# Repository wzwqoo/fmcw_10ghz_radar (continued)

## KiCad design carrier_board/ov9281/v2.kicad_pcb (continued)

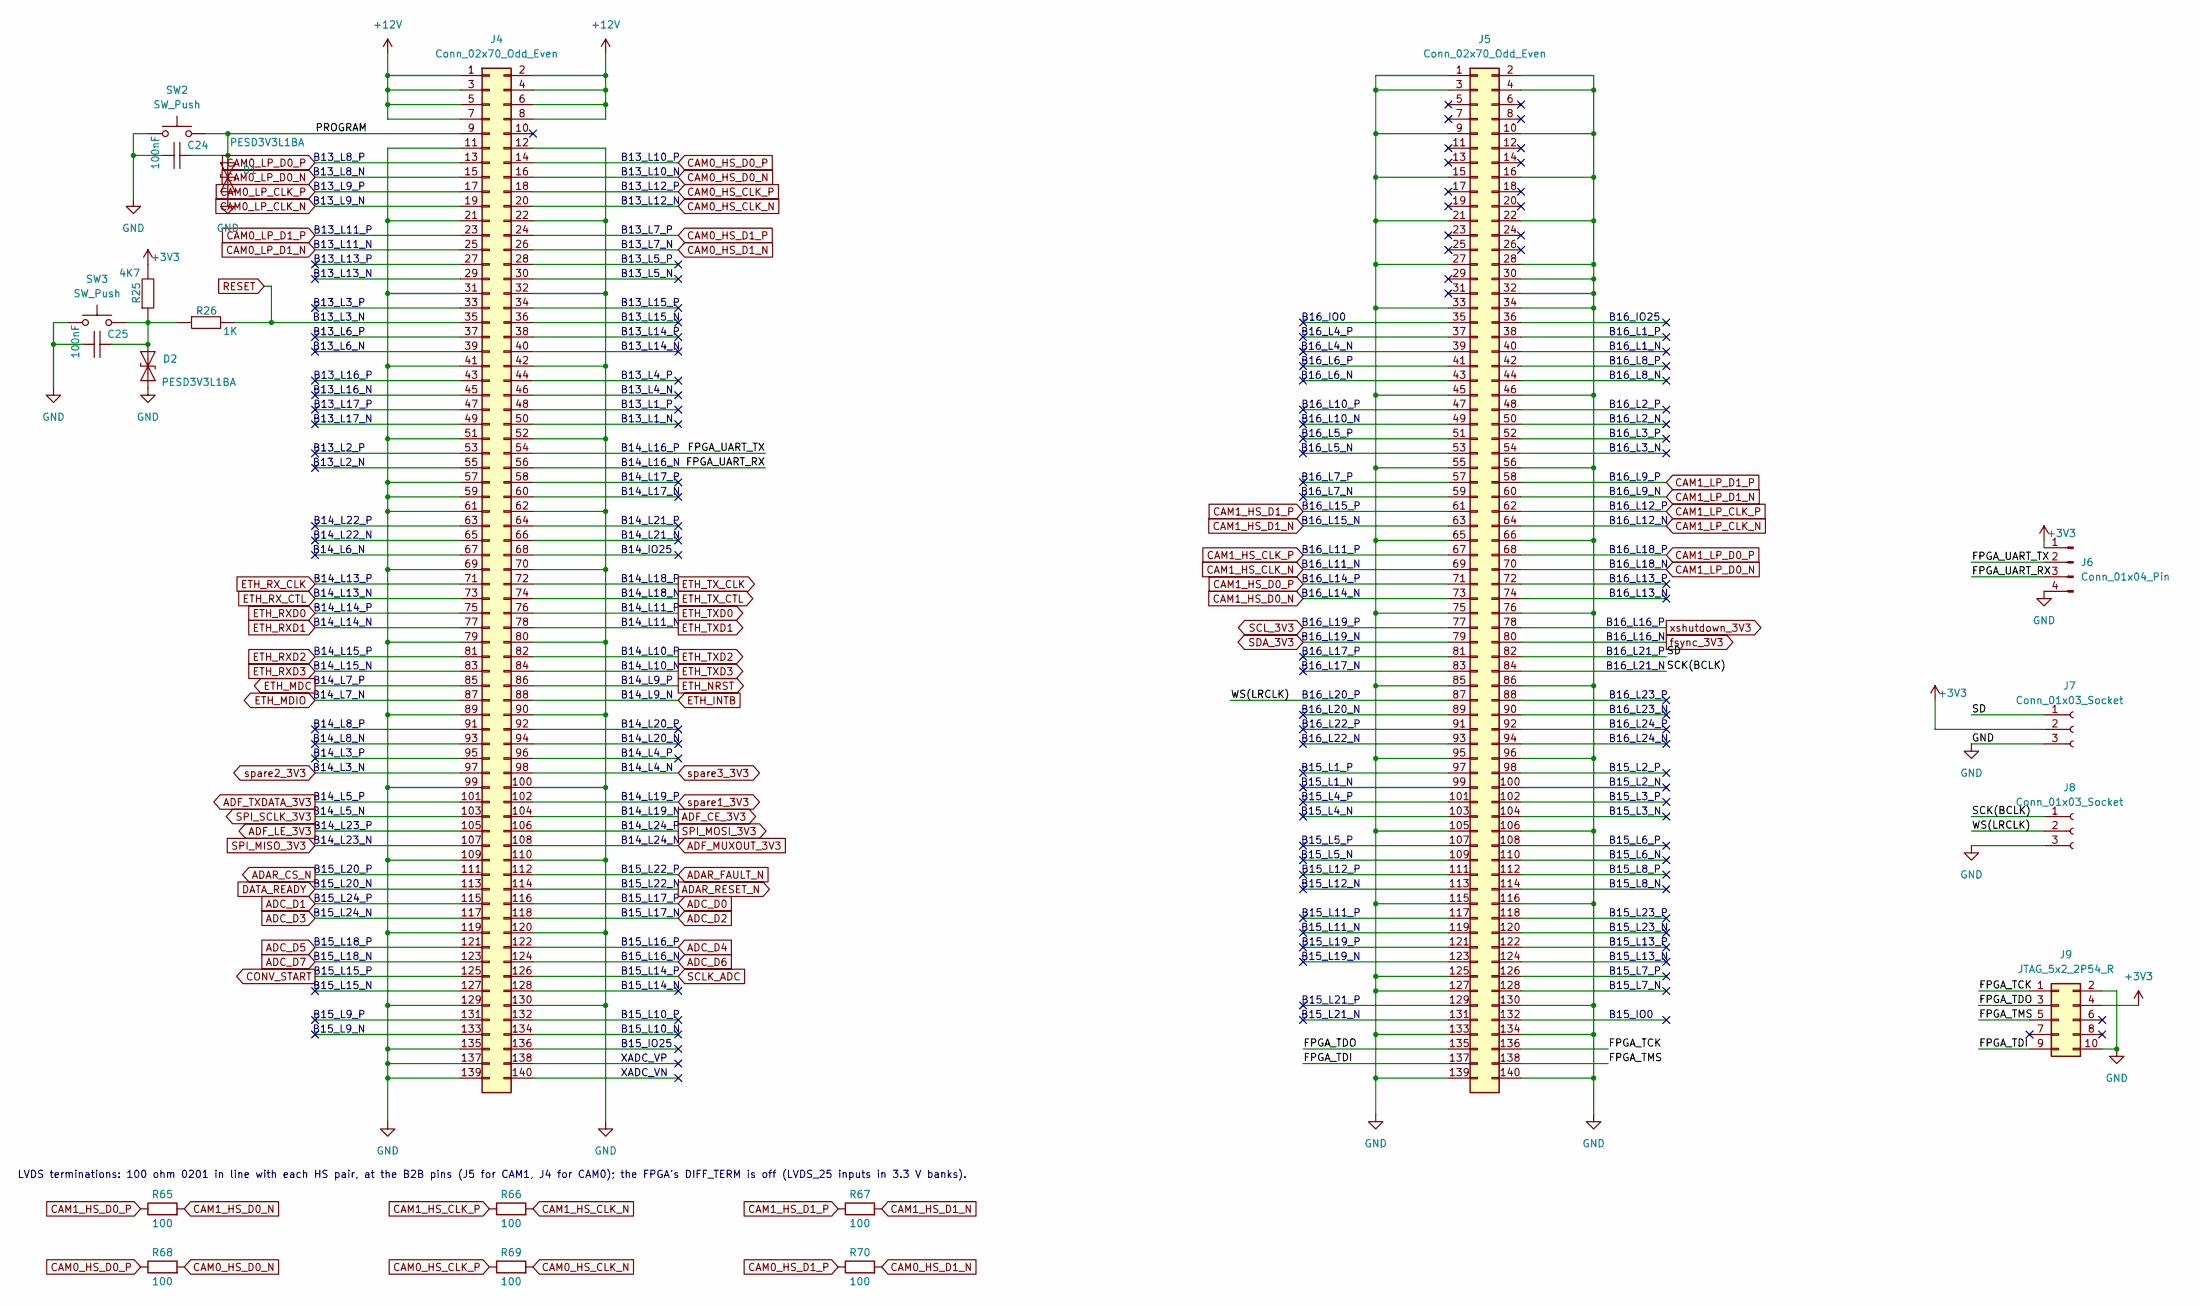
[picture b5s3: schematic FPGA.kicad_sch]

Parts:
C24, C25: 100nF; C_0805_2012Metric; TOLERANCE ±10%; RATINGS 16V; X7R; MANUFACTURER PART NUMBE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 CC0402KRX7R7BB103; LCSC Part # x
D1, D2: PESD3V3L1BA; D_SOD-323; Part# PESD3V3L1BA; LCSC Part # C54334012
J4, J5: Conn_02x70_Odd_Even; CONN-SMD_140P-P0.50_B2BM-2X70-0P5_BZOOC; Part# x; LCSC Part # x
J6: Conn_01x04_Pin; PinHeader_1x04_P2.54mm_Vertical; Part# x; LCSC Part # x
J7, J8: Conn_01x03_Socket; PinSocket_1x03_P2.54mm_Vertical; Part# x; LCSC Part # x
J9: JTAG_5x2_2P54_R; PinHeader_2x05_P2.54mm_Horizontal; Part# TSW-105-08-F-D-RA; LCSC Part # C6292590
R25: 4K7; R_0805_2012Metric; RATINGS 1/16 W; TOLERANCE ±5%; MANUFACTURER PART NUMBE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 RC0402JR-073K3L; LCSC Part # x
R26: 1K; R_0805_2012Metric; RATINGS 1/16 W; TOLERANCE ±5%; MANUFACTURER PART NUMBE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 RC0402JR-073K3L; LCSC Part # C100046
R65, R66, R67, R68, R69, R70: 100; R_0201_inline
SW2, SW3: SW_Push; SW_Push_SPST_NO_Alps_SKRK; Part# SKRKAHE020; LCSC Part # C202388

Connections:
+3V3: J6.1, J7.2, J9.4, R25.2; also elsewhere on the board
+12V: J4.1, J4.2, J4.3, J4.4, J4.5, J4.6, J4.7, J4.8; also elsewhere on the board
/FPGA/FPGA_TCK: J5.136, J9.1
/FPGA/FPGA_TDI: J5.137, J9.9
/FPGA/FPGA_TDO: J5.135, J9.3
/FPGA/FPGA_TMS: J5.138, J9.5
/FPGA/FPGA_UART_RX: J4.56, J6.3
/FPGA/FPGA_UART_TX: J4.54, J6.2
/FPGA/PROGRAM: C24.1, D1.2 (A2), J4.9, SW2.2
/FPGA/SCK(BCLK): J5.84, J8.1
/FPGA/SD: J5.82, J7.1
/FPGA/WS(LRCLK): J5.87, J8.2
ADAR_CS_N: J4.111; also elsewhere on the board
ADAR_FAULT_N: J4.112; also elsewhere on the board
ADAR_RESET_N: J4.114; also elsewhere on the board
ADC_D0: J4.116; also elsewhere on the board
ADC_D1: J4.115; also elsewhere on the board
ADC_D2: J4.118; also elsewhere on the board
ADC_D3: J4.117; also elsewhere on the board
ADC_D4: J4.122; also elsewhere on the board
ADC_D5: J4.121; also elsewhere on the board
ADC_D6: J4.124; also elsewhere on the board
ADC_D7: J4.123; also elsewhere on the board
ADF_CE_3V3: J4.104; also elsewhere on the board
ADF_LE_3V3: J4.105; also elsewhere on the board
ADF_MUXOUT_3V3: J4.108; also elsewhere on the board
ADF_TXDATA_3V3: J4.101; also elsewhere on the board
CAM0_HS_CLK_N: J4.20, R69.2; also elsewhere on the board
CAM0_HS_CLK_P: J4.18, R69.1; also elsewhere on the board
CAM0_HS_D0_N: J4.16, R68.2; also elsewhere on the board
CAM0_HS_D0_P: J4.14, R68.1; also elsewhere on the board
CAM0_HS_D1_N: J4.26, R70.2; also elsewhere on the board
CAM0_HS_D1_P: J4.24, R70.1; also elsewhere on the board
CAM0_LP_CLK_N: J4.19; also elsewhere on the board
CAM0_LP_CLK_P: J4.17; also elsewhere on the board
CAM0_LP_D0_N: J4.15; also elsewhere on the board
CAM0_LP_D0_P: J4.13; also elsewhere on the board
CAM0_LP_D1_N: J4.25; also elsewhere on the board
CAM0_LP_D1_P: J4.23; also elsewhere on the board
CAM1_HS_CLK_N: J5.69, R66.2; also elsewhere on the board
CAM1_HS_CLK_P: J5.67, R66.1; also elsewhere on the board
CAM1_HS_D0_N: J5.73, R65.2; also elsewhere on the board
CAM1_HS_D0_P: J5.71, R65.1; also elsewhere on the board
CAM1_HS_D1_N: J5.63, R67.2; also elsewhere on the board
CAM1_HS_D1_P: J5.61, R67.1; also elsewhere on the board
CAM1_LP_CLK_N: J5.64; also elsewhere on the board
CAM1_LP_CLK_P: J5.62; also elsewhere on the board
CAM1_LP_D0_N: J5.70; also elsewhere on the board
CAM1_LP_D0_P: J5.68; also elsewhere on the board
CAM1_LP_D1_N: J5.60; also elsewhere on the board
CAM1_LP_D1_P: J5.58; also elsewhere on the board
CONV_START: J4.125; also elsewhere on the board
DATA_READY: J4.113; also elsewhere on the board
ETH_INTB: J4.88; also elsewhere on the board
ETH_MDC: J4.85; also elsewhere on the board
ETH_MDIO: J4.87; also elsewhere on the board
ETH_NRST: J4.86; also elsewhere on the board
ETH_RXD0: J4.75; also elsewhere on the board
ETH_RXD1: J4.77; also elsewhere on the board
ETH_RXD2: J4.81; also elsewhere on the board
ETH_RXD3: J4.83; also elsewhere on the board
ETH_RX_CLK: J4.71; also elsewhere on the board
ETH_RX_CTL: J4.73; also elsewhere on the board
ETH_TXD0: J4.76; also elsewhere on the board
ETH_TXD1: J4.78; also elsewhere on the board
ETH_TXD2: J4.82; also elsewhere on the board
ETH_TXD3: J4.84; also elsewhere on the board
ETH_TX_CLK: J4.72; also elsewhere on the board
ETH_TX_CTL: J4.74; also elsewhere on the board
GND: C24.2, C25.2, D1.1 (A1), D2.1 (A1), J4.11, J4.12, J4.21, J4.22, J4.31, J4.32, J4.41, J4.42, J4.51, J4.52, J4.57, J4.59, J4.61, J4.62, J4.69, J4.70, J4.79, J4.80, J4.89, J4.90, J4.99, J4.100, J4.109, J4.110, J4.119, J4.120, J4.129, J4.130, J4.135, J4.137, J4.139, J5.1, J5.2, J5.3, J5.4, J5.9, J5.10, J5.15, J5.16, J5.21, J5.22, J5.27, J5.28, J5.30, J5.32, J5.33, J5.34, J5.45, J5.46, J5.55, J5.56, J5.65, J5.66, J5.75, J5.76, J5.85, J5.86, J5.95, J5.96, J5.105, J5.106, J5.115, J5.116, J5.125, J5.127, J5.130, J5.133, J5.134, J5.139, J5.140, J6.4, J7.3, J8.3, J9.2, J9.10, SW2.1, SW3.1; also elsewhere on the board
unnamed: C25.1, D2.2 (A2), R25.1, R26.1, SW3.2
RESET: J4.35, R26.2; also elsewhere on the board
SCLK_ADC: J4.126; also elsewhere on the board
SCL_3V3: J5.77; also elsewhere on the board
SDA_3V3: J5.79; also elsewhere on the board
SPI_MISO_3V3: J4.107; also elsewhere on the board
SPI_MOSI_3V3: J4.106; also elsewhere on the board
SPI_SCLK_3V3: J4.103; also elsewhere on the board
fsync_3V3: J5.80; also elsewhere on the board
spare1_3V3: J4.102; also elsewhere on the board
spare2_3V3: J4.97; also elsewhere on the board
spare3_3V3: J4.98; also elsewhere on the board
xshutdown_3V3: J5.78; also elsewhere on the board

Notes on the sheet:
B16_L14_N
B14_L24_P
B14_L15_P
B16_L1_P
B14_L22_N
B15_L5_P
B16_L3_P
B16_L13_N
B15_L17_N
B13_L6_P
B16_L21_N
B14_L14_P
B15_L1_N
B13_L2_P
B15_L24_P
B15_L15_P
B14_IO25
B16_L20_P
B14_L18_P
B13_L13_N
B16_L24_N
B15_L7_P
B13_L16_N
B13_L13_P
B15_L11_N
B15_L21_N
B15_L22_P
B15_L20_P
B13_L1_P
B14_L9_P
B13_L4_P
B13_L14_N
B15_L14_P
B15_L24_N
B16_L11_P
B14_L3_P
B15_L8_N
B13_L8_N
B13_L14_P
B15_L23_P

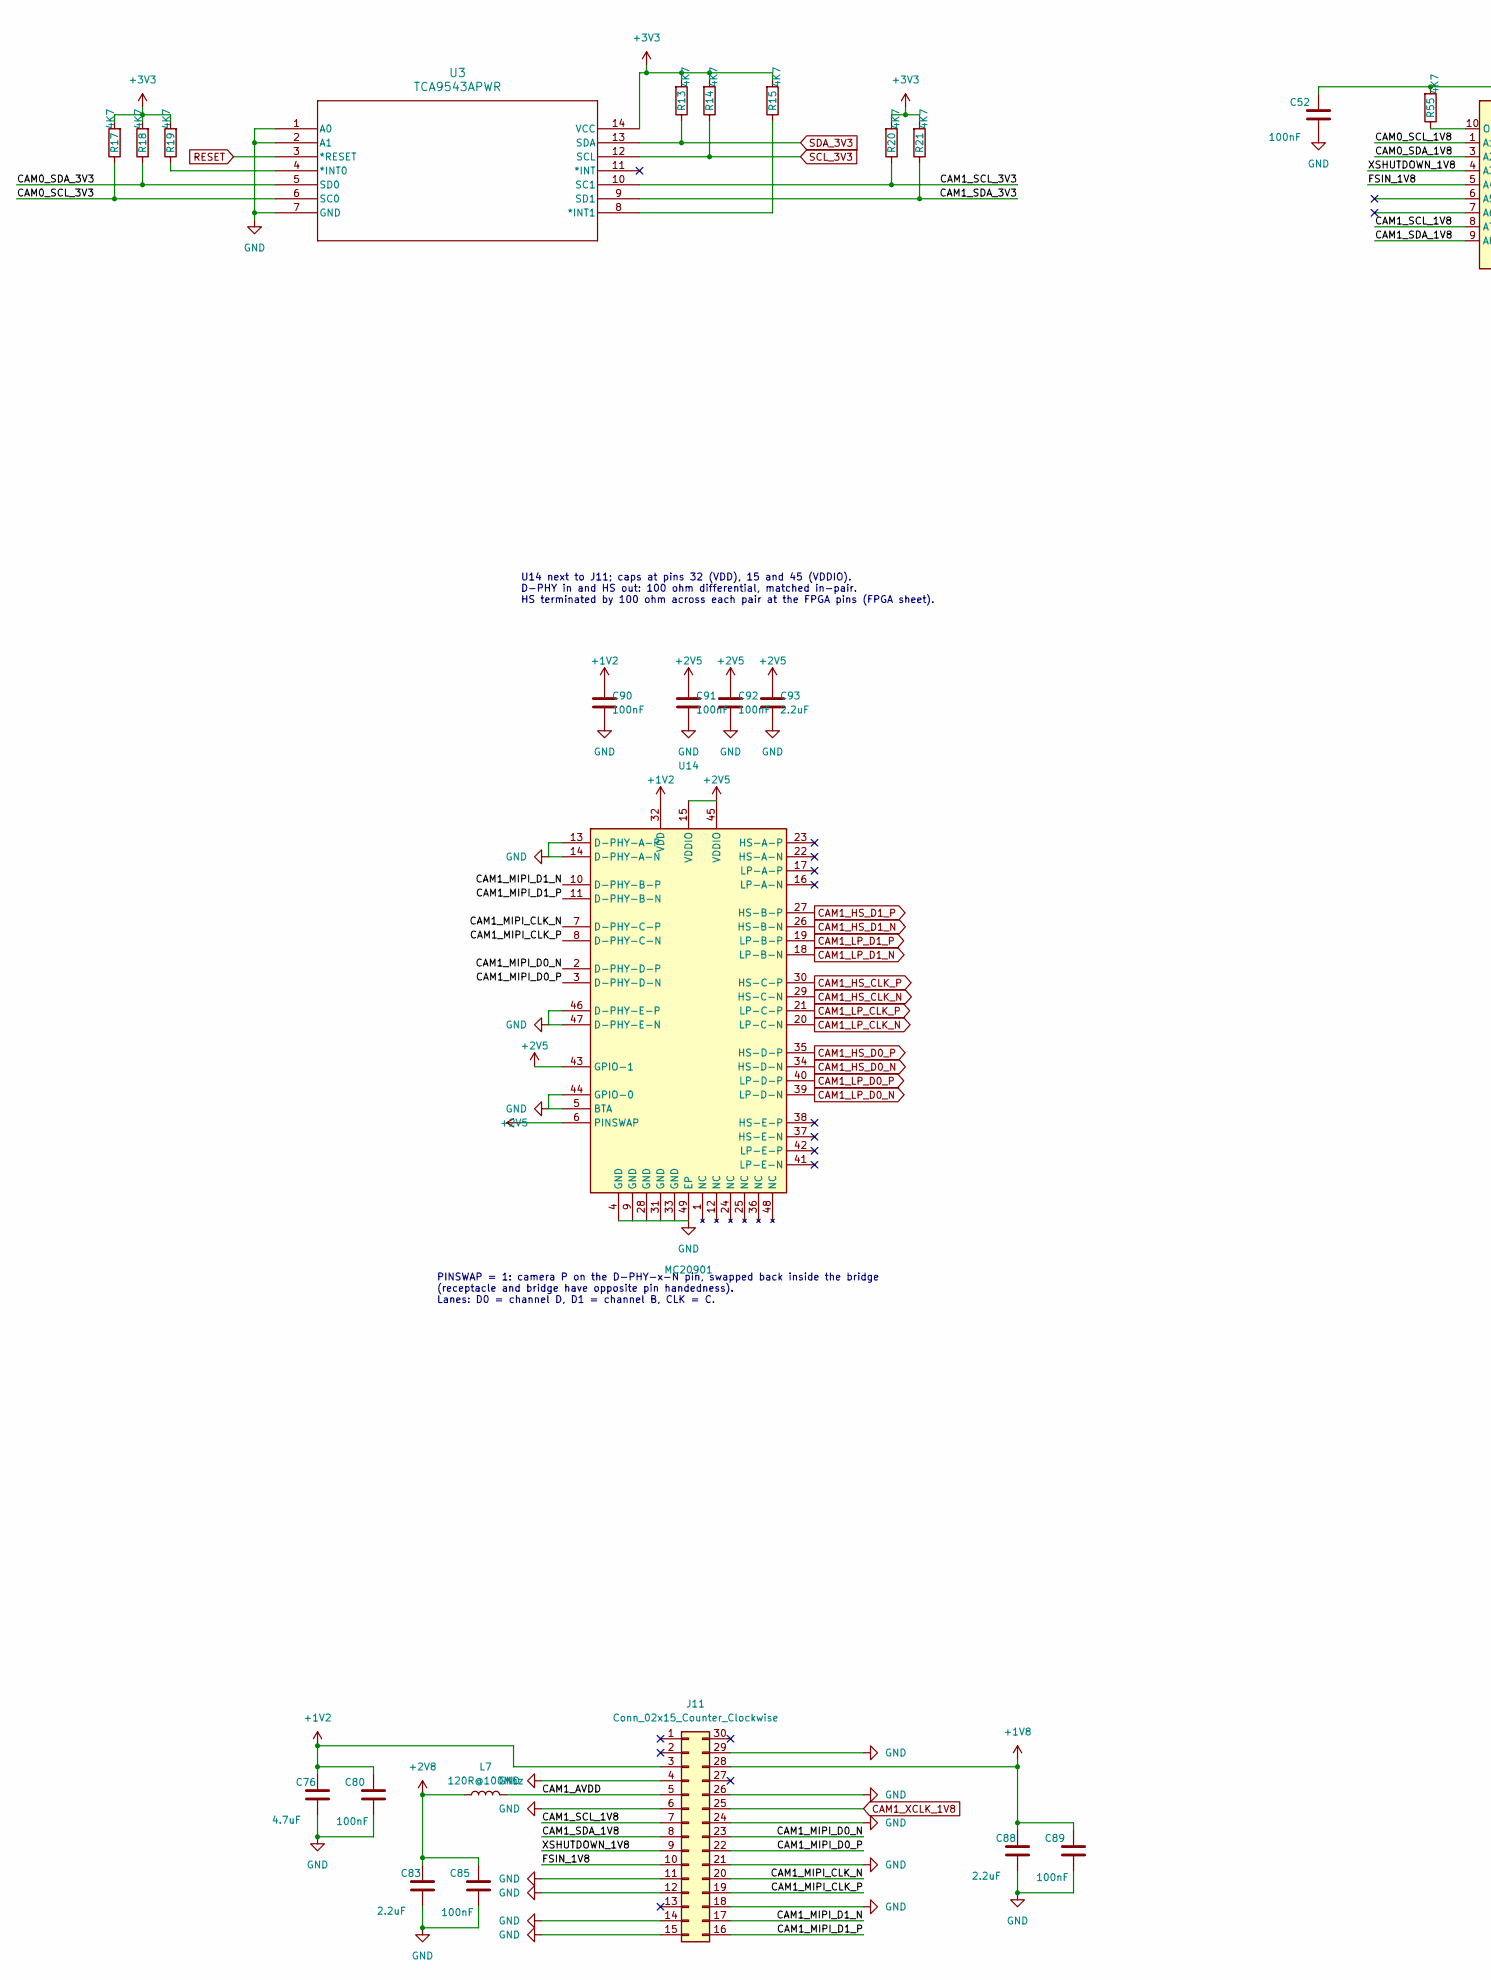
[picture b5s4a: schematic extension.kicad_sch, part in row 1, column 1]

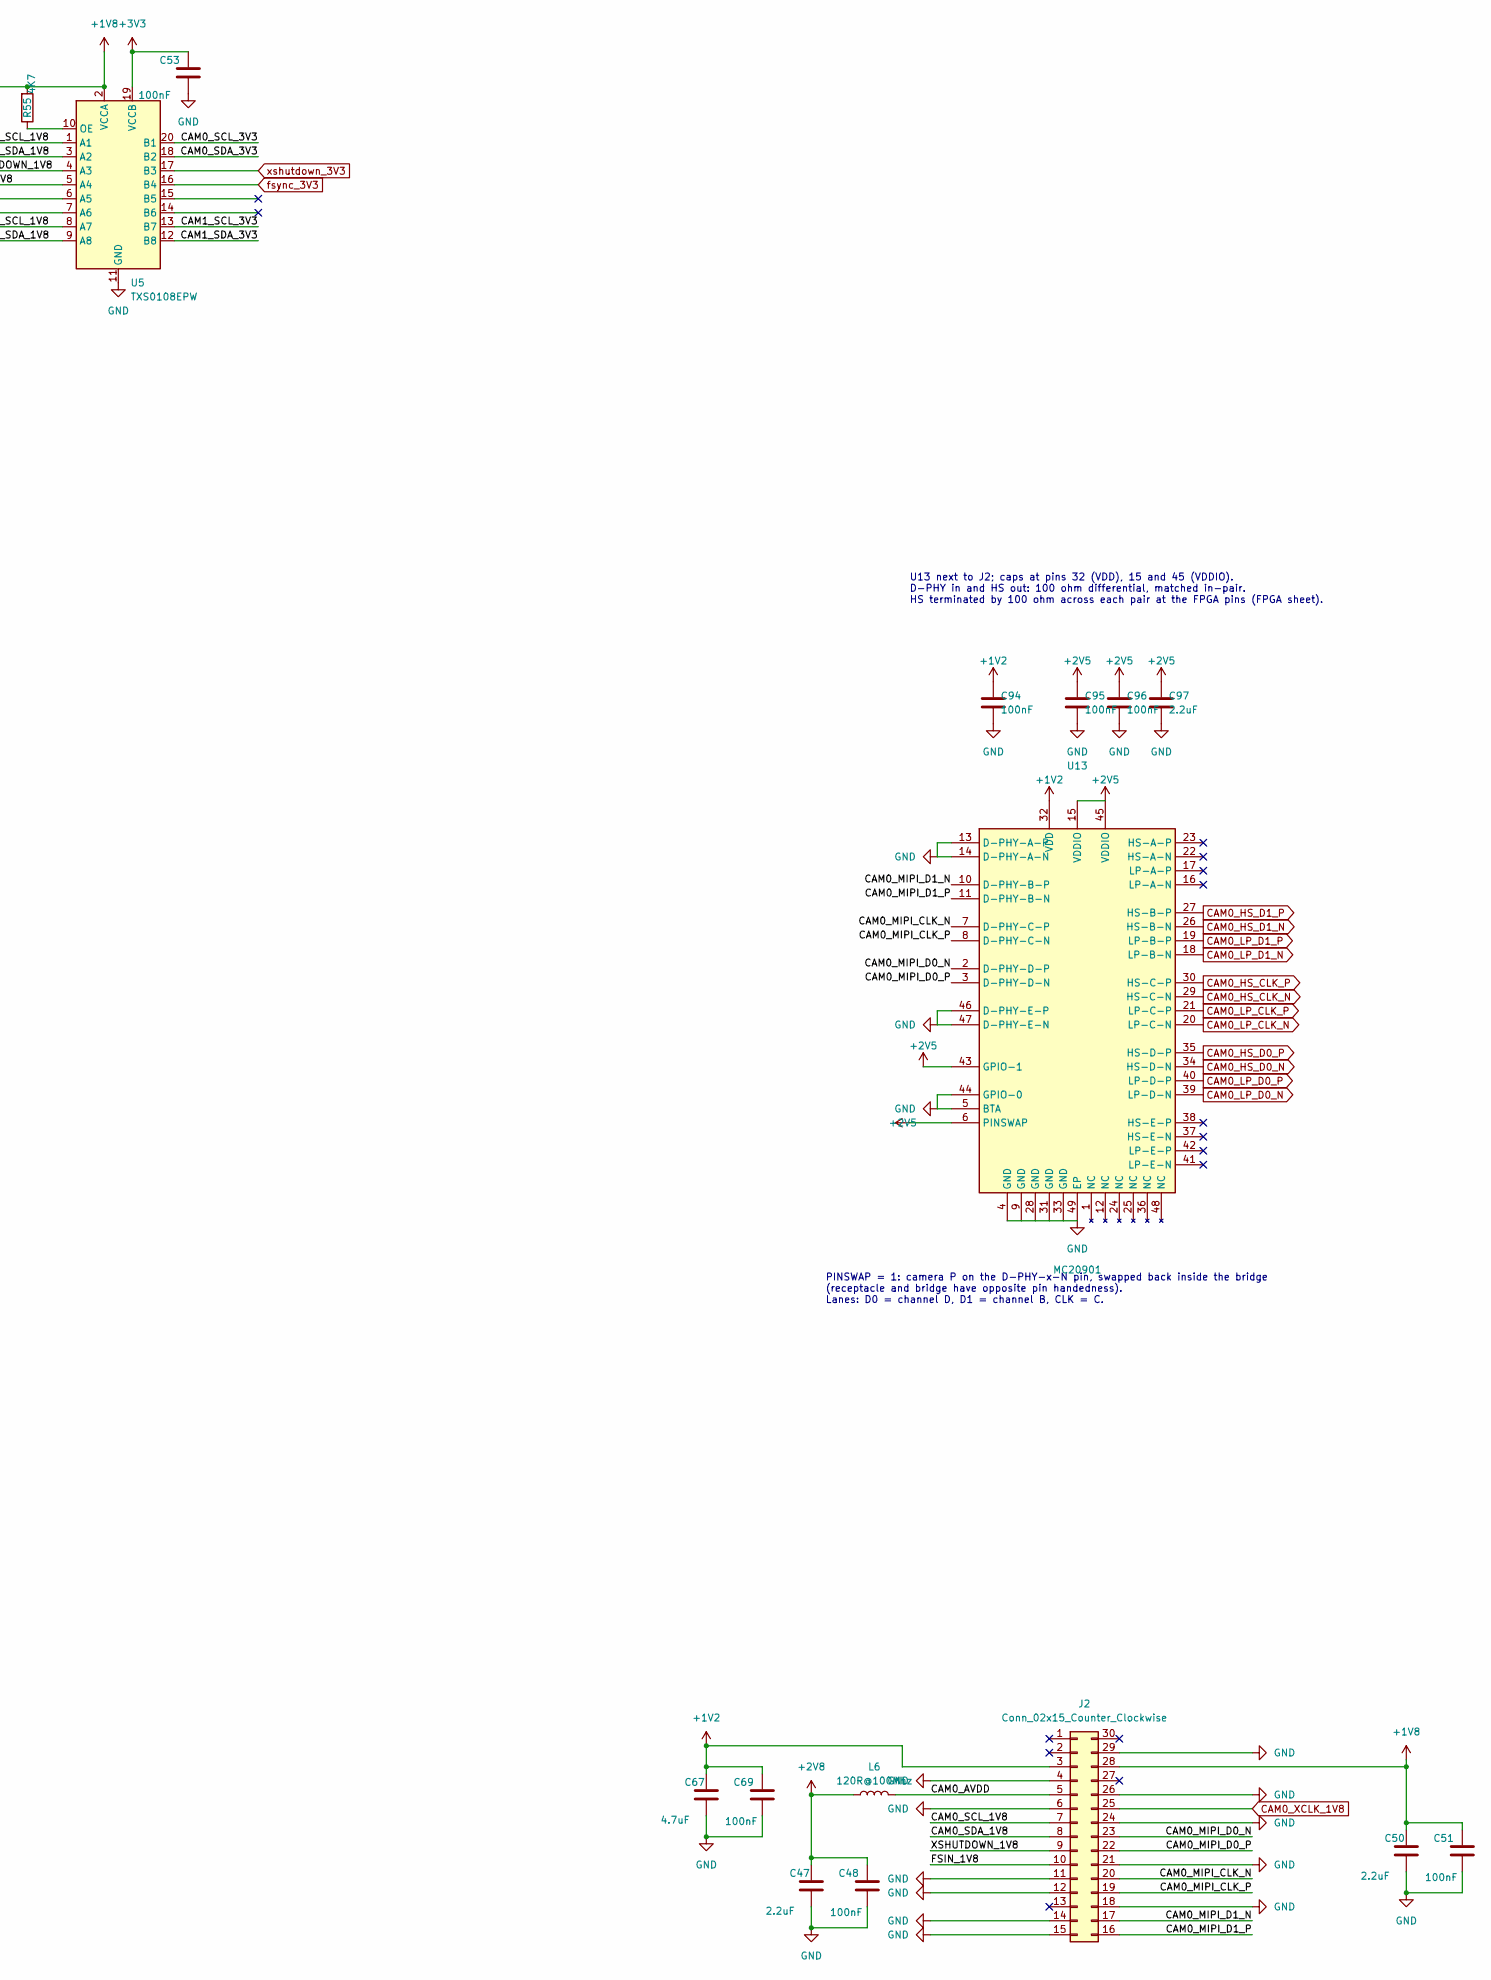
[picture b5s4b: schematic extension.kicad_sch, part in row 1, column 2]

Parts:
C47, C50, C83, C88: 2.2uF; C_0805_2012Metric; Part# x; LCSC Part # x
C48, C51, C52, C53, C69, C80, C85, C89: 100nF; C_0805_2012Metric; Part# x; LCSC Part # x
C67, C76: 4.7uF; C_0805_2012Metric
C90, C91, C92, C94, C95, C96: 100nF; C_0402_1005Metric
C93, C97: 2.2uF; C_0805_2012Metric
J2, J11: Conn_02x15_Counter_Clockwise; CAM_B2B_30P_placeholder; Part# x; LCSC Part # x
L6, L7: 120R@100Mhz; L_0805_2012Metric; Part# UPZ2012E121-4R0TF; LCSC Part # C97001
R13, R14, R15, R17, R18, R19, R20, R21, R55: 4K7; R_0805_2012Metric; Part# x; LCSC Part # x
U3: TCA9543APWR; TSSOP-14_4.4x5mm_P0.65mm; LCSC Part # C2653307
U5: TXS0108EPW; TSSOP-20_4.4x6.5mm_P0.65mm; LCSC Part # C17206
U13, U14: MC20901; MC20901_TQLMP-48_7x7mm_P0.5mm_EP5.6x5.6mm

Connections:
+1V2: C67.1, C69.1, C76.1, C80.1, C90.1, C94.1, J2.3, J11.3, U13.32 (VDD), U14.32 (VDD); also elsewhere on the board
+1V8: C50.1, C51.1, C52.1, C88.1, C89.1, J2.28, J11.28, R55.2, U5.2 (VCCA); also elsewhere on the board
+2V5: C91.1, C92.1, C93.1, C95.1, C96.1, C97.1, U13.6 (PINSWAP), U13.15 (VDDIO), U13.43 (GPIO-1), U13.45 (VDDIO), U14.6 (PINSWAP), U14.15 (VDDIO), U14.43 (GPIO-1), U14.45 (VDDIO); also elsewhere on the board
+2V8: C47.1, C48.1, C83.1, C85.1, L6.1, L7.1; also elsewhere on the board
+3V3: C53.1, R13.2, R14.2, R15.2, R17.2, R18.2, R19.2, R20.2, R21.2, U3.14 (VCC), U5.19 (VCCB); also elsewhere on the board
/CAM/CAM0_AVDD: J2.5, L6.2
/CAM/CAM0_MIPI_CLK_N: J2.20, U13.7 (D-PHY-C-P)
/CAM/CAM0_MIPI_CLK_P: J2.19, U13.8 (D-PHY-C-N)
/CAM/CAM0_MIPI_D0_N: J2.23, U13.2 (D-PHY-D-P)
/CAM/CAM0_MIPI_D0_P: J2.22, U13.3 (D-PHY-D-N)
/CAM/CAM0_MIPI_D1_N: J2.17, U13.10 (D-PHY-B-P)
/CAM/CAM0_MIPI_D1_P: J2.16, U13.11 (D-PHY-B-N)
/CAM/CAM0_SCL_1V8: J2.7, U5.1 (A1)
/CAM/CAM0_SCL_3V3: R17.1, U3.6 (SC0), U5.20 (B1)
/CAM/CAM0_SDA_1V8: J2.8, U5.3 (A2)
/CAM/CAM0_SDA_3V3: R18.1, U3.5 (SD0), U5.18 (B2)
/CAM/CAM1_AVDD: J11.5, L7.2
/CAM/CAM1_MIPI_CLK_N: J11.20, U14.7 (D-PHY-C-P)
/CAM/CAM1_MIPI_CLK_P: J11.19, U14.8 (D-PHY-C-N)
/CAM/CAM1_MIPI_D0_N: J11.23, U14.2 (D-PHY-D-P)
/CAM/CAM1_MIPI_D0_P: J11.22, U14.3 (D-PHY-D-N)
/CAM/CAM1_MIPI_D1_N: J11.17, U14.10 (D-PHY-B-P)
/CAM/CAM1_MIPI_D1_P: J11.16, U14.11 (D-PHY-B-N)
/CAM/CAM1_SCL_1V8: J11.7, U5.8 (A7)
/CAM/CAM1_SCL_3V3: R20.1, U3.10 (SC1), U5.13 (B7)
/CAM/CAM1_SDA_1V8: J11.8, U5.9 (A8)
/CAM/CAM1_SDA_3V3: R21.1, U3.9 (SD1), U5.12 (B8)
/CAM/FSIN_1V8: J2.10, J11.10, U5.5 (A4)
/CAM/XSHUTDOWN_1V8: J2.9, J11.9, U5.4 (A3)
CAM0_HS_CLK_N: U13.29 (HS-C-N); also elsewhere on the board
CAM0_HS_CLK_P: U13.30 (HS-C-P); also elsewhere on the board
CAM0_HS_D0_N: U13.34 (HS-D-N); also elsewhere on the board
CAM0_HS_D0_P: U13.35 (HS-D-P); also elsewhere on the board
CAM0_HS_D1_N: U13.26 (HS-B-N); also elsewhere on the board
CAM0_HS_D1_P: U13.27 (HS-B-P); also elsewhere on the board
CAM0_LP_CLK_N: U13.20 (LP-C-N); also elsewhere on the board
CAM0_LP_CLK_P: U13.21 (LP-C-P); also elsewhere on the board
CAM0_LP_D0_N: U13.39 (LP-D-N); also elsewhere on the board
CAM0_LP_D0_P: U13.40 (LP-D-P); also elsewhere on the board
CAM0_LP_D1_N: U13.18 (LP-B-N); also elsewhere on the board
CAM0_LP_D1_P: U13.19 (LP-B-P); also elsewhere on the board
CAM0_XCLK_1V8: J2.25; also elsewhere on the board
CAM1_HS_CLK_N: U14.29 (HS-C-N); also elsewhere on the board
CAM1_HS_CLK_P: U14.30 (HS-C-P); also elsewhere on the board
CAM1_HS_D0_N: U14.34 (HS-D-N); also elsewhere on the board
CAM1_HS_D0_P: U14.35 (HS-D-P); also elsewhere on the board
CAM1_HS_D1_N: U14.26 (HS-B-N); also elsewhere on the board
CAM1_HS_D1_P: U14.27 (HS-B-P); also elsewhere on the board
CAM1_LP_CLK_N: U14.20 (LP-C-N); also elsewhere on the board
CAM1_LP_CLK_P: U14.21 (LP-C-P); also elsewhere on the board
CAM1_LP_D0_N: U14.39 (LP-D-N); also elsewhere on the board
CAM1_LP_D0_P: U14.40 (LP-D-P); also elsewhere on the board
CAM1_LP_D1_N: U14.18 (LP-B-N); also elsewhere on the board
CAM1_LP_D1_P: U14.19 (LP-B-P); also elsewhere on the board
CAM1_XCLK_1V8: J11.25; also elsewhere on the board
GND: C47.2, C48.2, C50.2, C51.2, C52.2, C53.2, C67.2, C69.2, C76.2, C80.2, C83.2, C85.2, C88.2, C89.2, C90.2, C91.2, C92.2, C93.2, C94.2, C95.2, C96.2, C97.2, J2.4, J2.6, J2.11, J2.12, J2.14, J2.15, J2.18, J2.21, J2.24, J2.26, J2.29, J11.4, J11.6, J11.11, J11.12, J11.14, J11.15, J11.18, J11.21, J11.24, J11.26, J11.29, U3.1 (A0), U3.2 (A1), U3.7 (GND), U5.11 (GND), U13.4 (GND), U13.5 (BTA), U13.9 (GND), U13.13 (D-PHY-A-P), U13.14 (D-PHY-A-N), U13.28 (GND), U13.31 (GND), U13.33 (GND), U13.44 (GPIO-0), U13.46 (D-PHY-E-P), U13.47 (D-PHY-E-N), U13.49 (EP), U14.4 (GND), U14.5 (BTA), U14.9 (GND), U14.13 (D-PHY-A-P), U14.14 (D-PHY-A-N), U14.28 (GND), U14.31 (GND), U14.33 (GND), U14.44 (GPIO-0), U14.46 (D-PHY-E-P), U14.47 (D-PHY-E-N), U14.49 (EP); also elsewhere on the board
unnamed: R19.1, U3.4 (*INT0)
unnamed: R15.1, U3.8 (*INT1)
unnamed: R55.1, U5.10 (OE)
RESET: U3.3 (*RESET); also elsewhere on the board
SCL_3V3: R14.1, U3.12 (SCL); also elsewhere on the board
SDA_3V3: R13.1, U3.13 (SDA); also elsewhere on the board
fsync_3V3: U5.16 (B4); also elsewhere on the board
xshutdown_3V3: U5.17 (B3); also elsewhere on the board

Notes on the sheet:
U14 next to J11; caps at pins 32 (VDD), 15 and 45 (VDDIO). D-PHY in and HS out: 100 ohm differential, matched in-pair. HS terminated by 100 ohm across each pair at the FPGA pins (FPGA sheet).
U13 next to J2; caps at pins 32 (VDD), 15 and 45 (VDDIO). D-PHY in and HS out: 100 ohm differential, matched in-pair. HS terminated by 100 ohm across each pair at the FPGA pins (FPGA sheet).
PINSWAP = 1: camera P on the D-PHY-x-N pin, swapped back inside the bridge (receptacle and bridge have opposite pin handedness). Lanes: D0 = channel D, D1 = channel B, CLK = C.

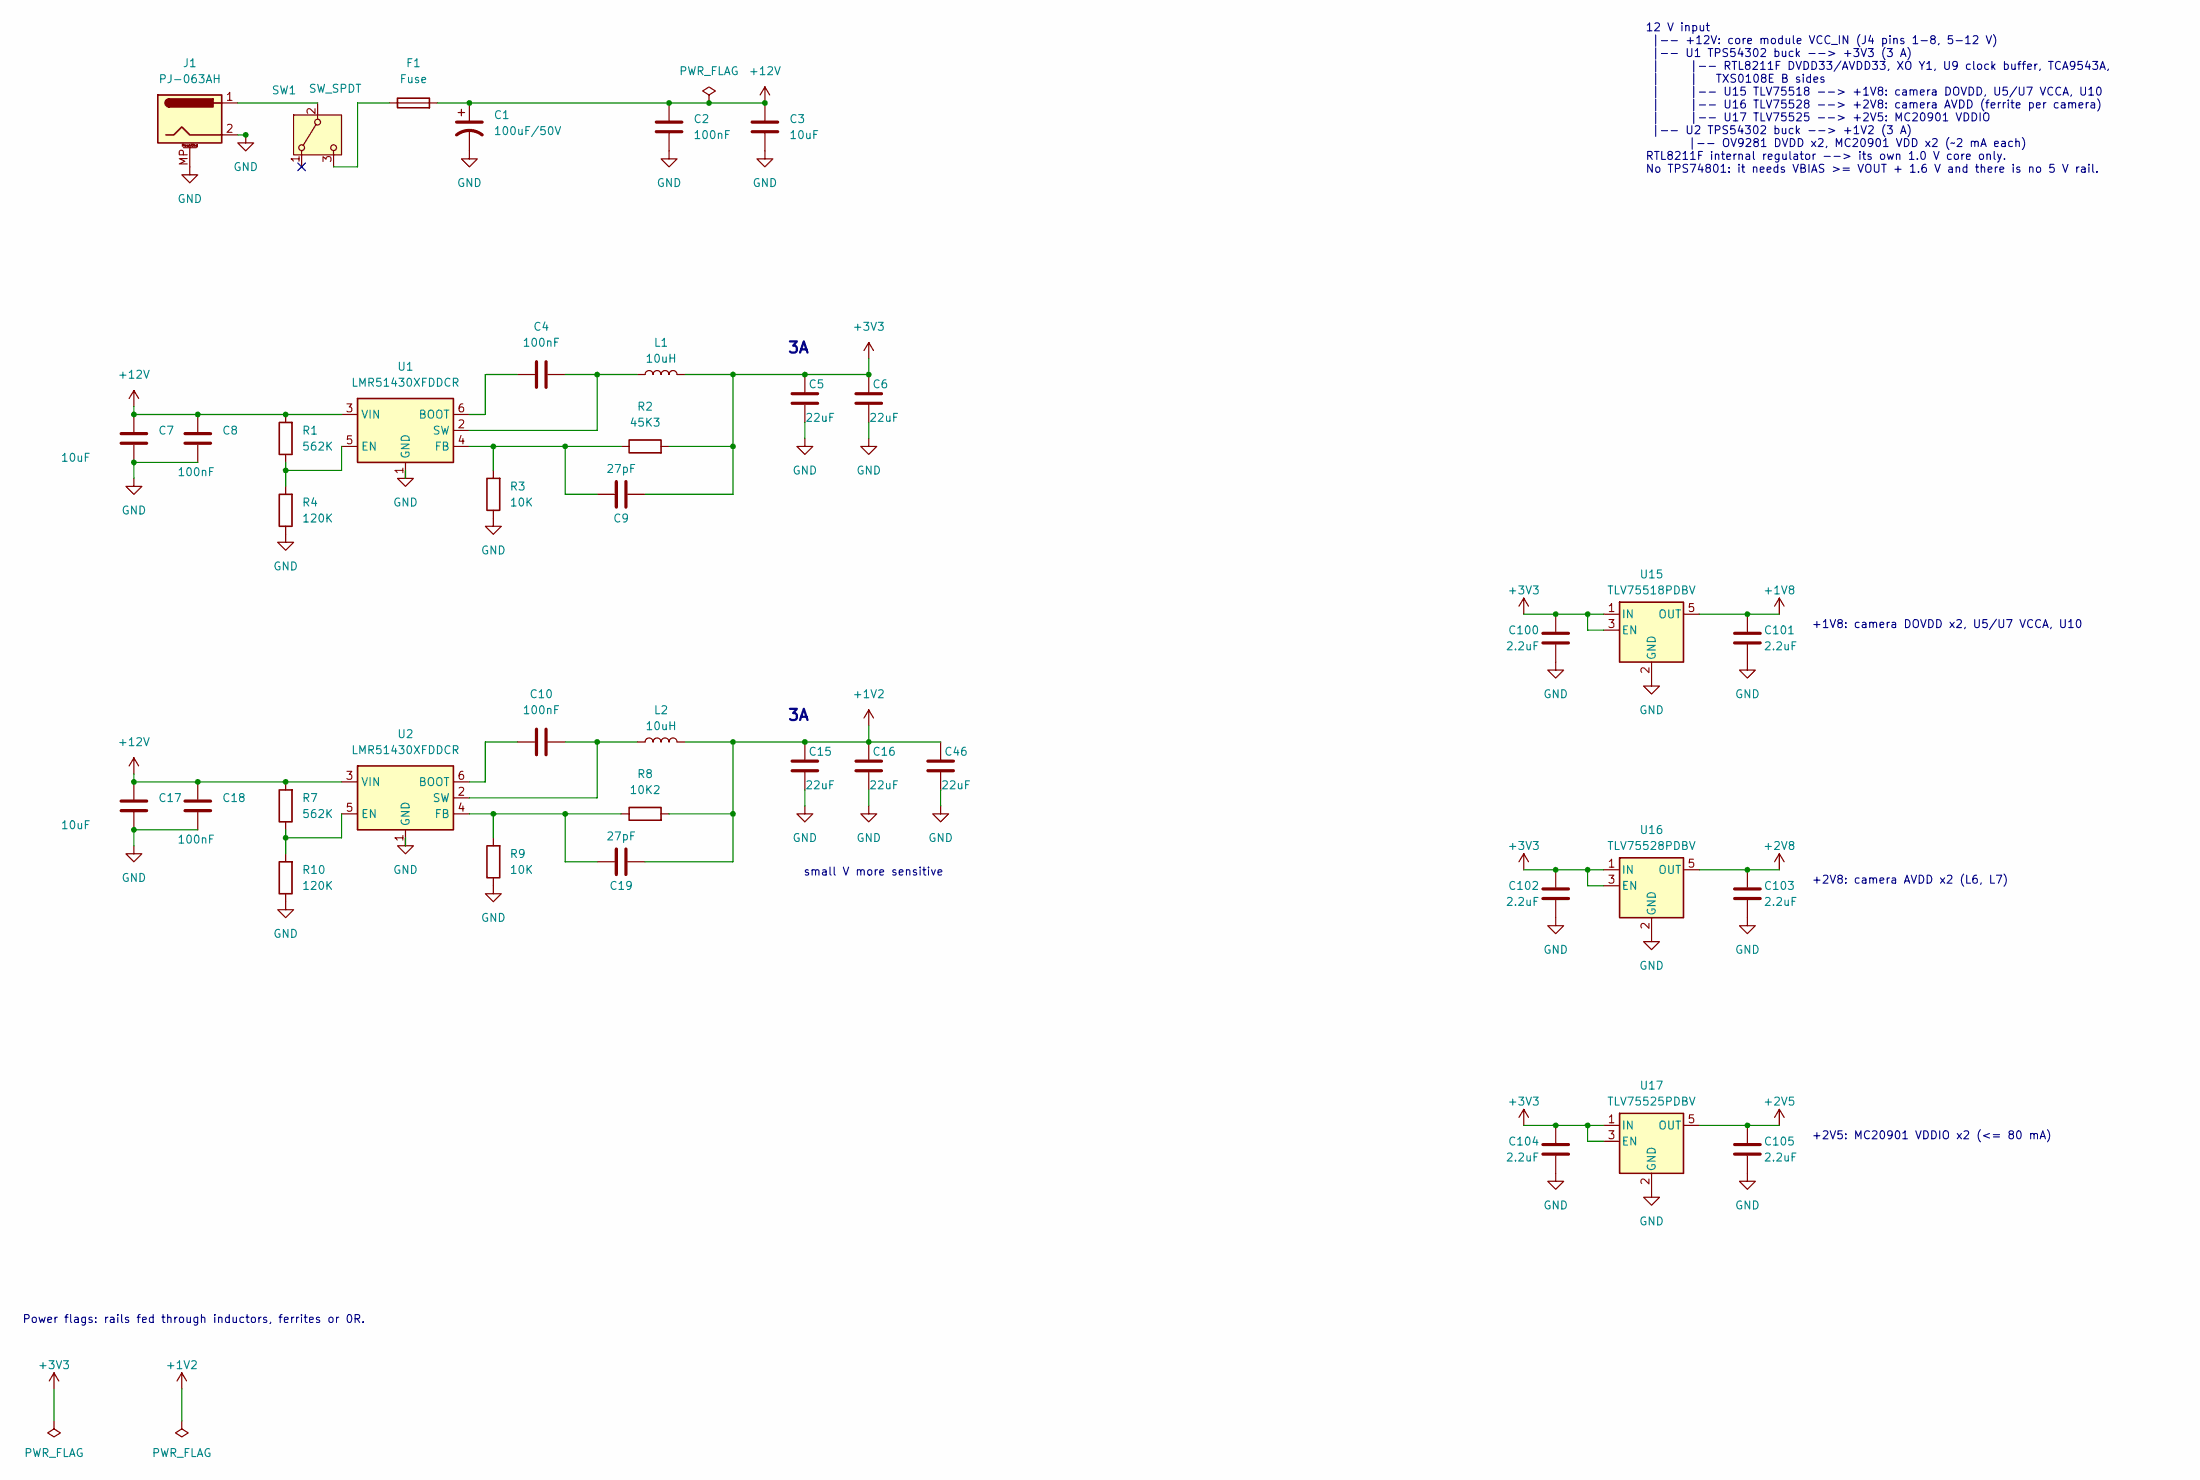
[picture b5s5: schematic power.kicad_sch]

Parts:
C1: 100uF/50V; CP_Elec_6.3x7.7; Part# JVJ50V100M6x8; LCSC Part # C46550415
C2, C4, C8, C10, C18: 100nF; C_0805_2012Metric; Part# x; LCSC Part # x
C3, C7, C17: 10uF; C_0805_2012Metric; Part# CC0805KKX5R8BB106; LCSC Part # C89831
C5, C6, C15, C16, C46: 22uF; C_0805_2012Metric; Part# CC0805MKX5R8BB226; LCSC Part # C784585
C9, C19: 27pF; C_0805_2012Metric; Part# x; LCSC Part # x
C100, C101, C102, C103, C104, C105: 2.2uF; C_0805_2012Metric
F1: Fuse; Fuse_1812_4532Metric; Part# SMD1812P200TF16; LCSC Part # C20812
J1: PJ-063AH; BarrelJack_CUI_PJ-063AH_Horizontal; Part# PJ-063AH
L1, L2: 10uH; L_Sunlord_MWSA0602S; Part# FXL0630-100-M; LCSC Part # C167223
R1, R7: 562K; R_0805_2012Metric; Part# x; LCSC Part # x
R2: 45K3; R_0805_2012Metric
R3: 10K; R_0805_2012Metric; Part# RT0805BRD0710KL
R4, R10: 120K; R_0805_2012Metric; Part# RC0805FR-07120KL; LCSC Part # C114524
R8: 10K2; R_0805_2012Metric; Part# RT0805BRD0710K2L
R9: 10K; R_0402_1005Metric; Part# RT0402BRD0710KL
SW1: SW_SPDT; SW-TH_3P-P4.80_HX-SS12D10G6-WJ; Part# SS12D10G6-WJ; LCSC Part # C7431059
U1, U2: LMR51430XFDDCR; TSOT-23-6; Part# LMR51430XFDDCR
U15: TLV75518PDBV; SOT-23-5
U16: TLV75528PDBV; SOT-23-5
U17: TLV75525PDBV; SOT-23-5

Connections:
+1V2: C15.1, C16.1, C19.2, C46.1, L2.2, R8.2; also elsewhere on the board
+1V8: C101.1, U15.5 (OUT); also elsewhere on the board
+2V5: C105.1, U17.5 (OUT); also elsewhere on the board
+2V8: C103.1, U16.5 (OUT); also elsewhere on the board
+3V3: C5.1, C6.1, C9.2, C100.1, C102.1, C104.1, L1.2, R2.2, U15.1 (IN), U15.3 (EN), U16.1 (IN), U16.3 (EN), U17.1 (IN), U17.3 (EN); also elsewhere on the board
+12V: C1.1, C2.1, C3.1, C7.1, C8.1, C17.1, C18.1, F1.2, R1.2, R7.2, U1.3 (VIN), U2.3 (VIN); also elsewhere on the board
GND: C1.2, C2.2, C3.2, C5.2, C6.2, C7.2, C8.2, C15.2, C16.2, C17.2, C18.2, C46.2, C100.2, C101.2, C102.2, C103.2, C104.2, C105.2, J1.2, J1.MP (MountPin), R3.1, R4.1, R9.1, R10.1, U1.1 (GND), U2.1 (GND), U15.2 (GND), U16.2 (GND), U17.2 (GND); also elsewhere on the board
unnamed: J1.1, SW1.2 (B)
unnamed: F1.1, SW1.3 (C)
unnamed: C4.1, U1.6 (BOOT)
unnamed: R1.1, R4.2, U1.5 (EN)
unnamed: C9.1, R2.1, R3.2, U1.4 (FB)
unnamed: C4.2, L1.1, U1.2 (SW)
unnamed: C10.1, U2.6 (BOOT)
unnamed: R7.1, R10.2, U2.5 (EN)
unnamed: C19.1, R8.1, R9.2, U2.4 (FB)
unnamed: C10.2, L2.1, U2.2 (SW)

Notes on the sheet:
small V more sensitive
+1V8: camera DOVDD x2, U5/U7 VCCA, U10
+2V8: camera AVDD x2 (L6, L7)
+2V5: MC20901 VDDIO x2 (<= 80 mA)
12 V input |-- +12V: core module VCC_IN (J4 pins 1-8, 5-12 V) |-- U1 TPS54302 buck --> +3V3 (3 A) | |-- RTL8211F DVDD33/AVDD33, XO Y1, U9 clock buffer, TCA9543A, | | TXS0108E B sides | |-- U15 TLV75518 --> +1V8: camera DOVDD, U5/U7 VCCA, U10 | |-- U16 TLV75528 --> +2V8: camera AVDD (ferrite per cam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
Power flags: rails fed through inductors, ferrites or 0R.

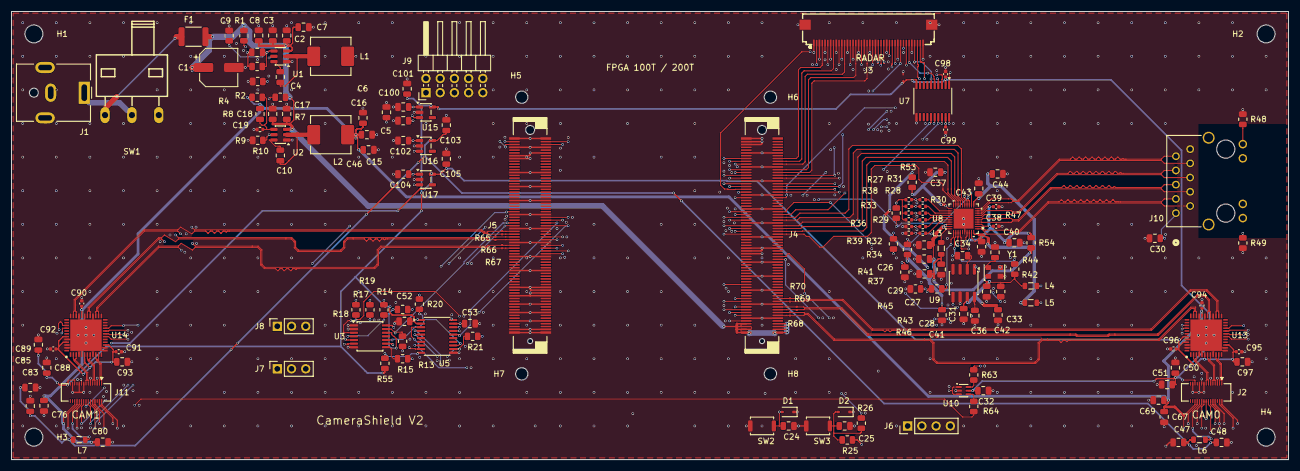
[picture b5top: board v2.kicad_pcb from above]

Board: 6 copper layers, 228.0 x 80.0 mm, 165 parts (0 on the bottom side), 166 nets.

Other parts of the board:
H1, H2, H3, H4: MountingHole_3.2mm_M3
H5, H6, H7, H8: MountingHole_2.2mm_M2
